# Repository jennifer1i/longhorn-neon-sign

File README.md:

# Neon Sign Interface Board RevB - Jennifer Li

## Board Description
- Compact 2-layer PCB for PWM-controlled LED driving using nMOSFET switching and onboard 12V->5V buck regulation. Revision of neon sign project from Summer 2025 with stronger consideration for manufacturability, testability, thermal management, compact routing, and aesthetics. 
## Features
- 12V input power architecture
- 12V->5V integrated buck converter
- Multi-channel nMOSFET LED control
- Arduino-Nano based LED toggling and dimming
- Optimized for compact and clean routing
- SMT/SMD and THT assembly
- Testpoints for GND, 12V, 5V, and PWM
- Indicator LEDs with blank silkscreen for post-production debugging

## Design Notes
- The PCB was designed to be rectangular, optimizing balanced LED power distribution and component placement. Testpoints and button switches were placed along the sides for easier access in the debugging process. 
- For this design, I chose to have two LED output terminals after evaluating the maximum load requirement of the targeted LED strips. The strips I chose draw up to 5A, and thus my output circuits were designed to handle up to roughly 2.5A.
- In addition, these two terminals were placed on opposite ends of the PCB's length to simplify high-current routing, reduce congestion, and distribute power evenly across the final neon sign product without unecessary harnessing cross-over. To accomodate this placement, I used a 12V pour on the top layer in an area with minimal top-layer GND pads and minimal top-layer routing. Thus, I could provide a clean low-impedance power distribution between the input stage and the LED ouptut terminal on the opposite end of the board. 
  
## PCB Specificaitions
- Layers: 2
- PCB Thickness: 1.6 mm
- Assembly: SMT/SMD and THT
- Designed in KiCad

## Future Improvements
- Switch to addressable LED strips for firmware-controlled animation and color effects
- Transition to a fully integrated MCU system (ESP32) directly mounted on the PCB
- Use lower-profile connectors like Molex Nanofits instead of screw terminals
- Rework the user input interface, using more ergonomic control interfaces like potentiometers, rotary encoders, or low-profile switches
- Add additional protection circuitry including input fuses, TVS diodes, reverse-polarity protection, and overvoltage and undervoltage protection
- Implement per-channel current sensing and thermal monitoring
- Enable PG pin for buck converter and add output sensing

## Top Layer

## Back Layer

## 3D Render

## Root Schematic

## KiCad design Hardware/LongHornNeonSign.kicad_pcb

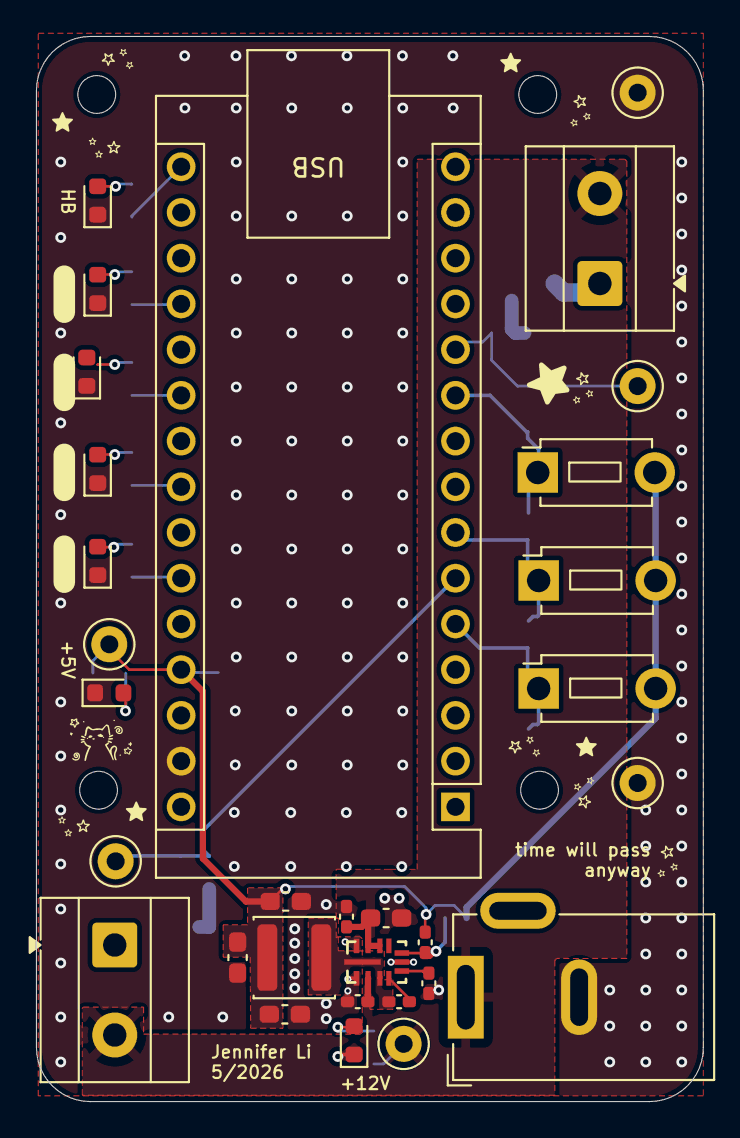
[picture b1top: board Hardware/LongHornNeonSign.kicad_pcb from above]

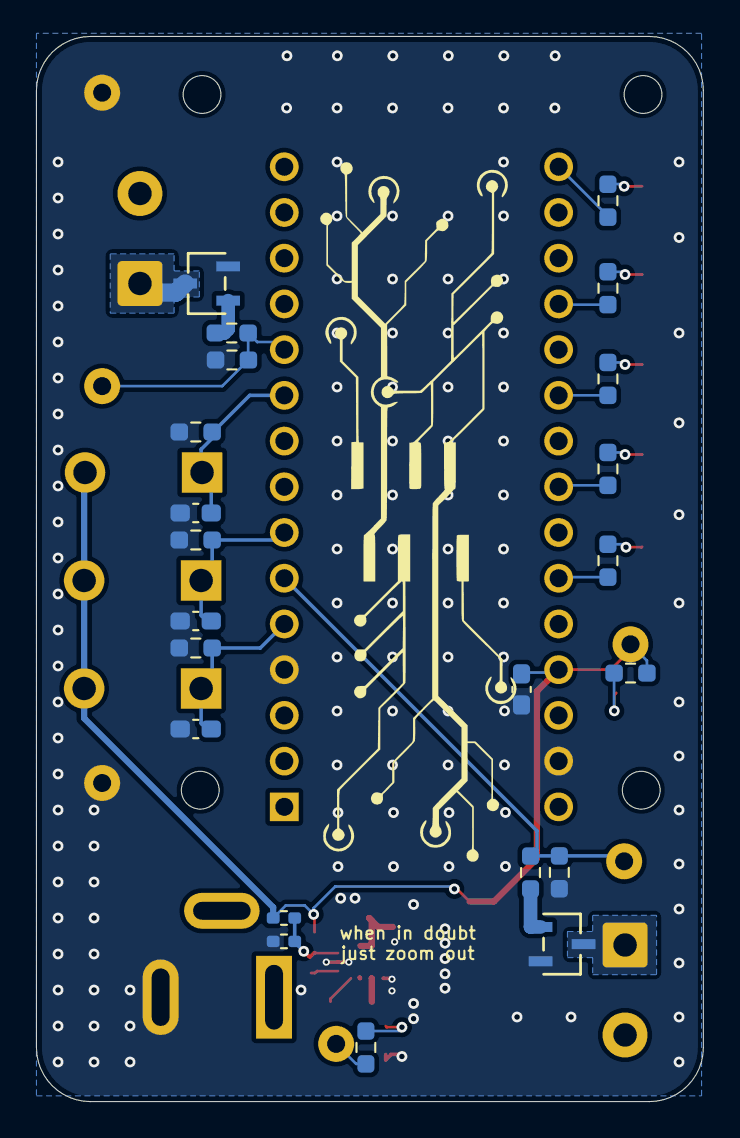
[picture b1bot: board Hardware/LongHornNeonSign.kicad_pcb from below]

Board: 2 copper layers, 37.0 x 59.2 mm, 57 parts (22 on the bottom side), 28 nets.

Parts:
A1: Arduino Nano; Arduino_Nano
C1, C11, C12, C13: 0.1uF; C_0603_1608Metric_Pad1.08x0.95mm_HandSolder
C2: 4.7u; C_0603_1608Metric_Pad1.08x0.95mm_HandSolder
C3, C4: 220n; C_0402_1005Metric_Pad0.74x0.62mm_HandSolder
C5: 1u; C_0402_1005Metric_Pad0.74x0.62mm_HandSolder
C6: .1u; C_0402_1005Metric_Pad0.74x0.62mm_HandSolder
C7: 20p; C_0402_1005Metric_Pad0.74x0.62mm_HandSolder
C8, C9, C10: 22u; C_0603_1608Metric_Pad1.08x0.95mm_HandSolder
D1, D2: LED_0603_1608Metric
D3, D4: LED2; LED_0603_1608Metric
D5: LED1; LED_0603_1608Metric
D6: LED0; LED_0603_1608Metric
D7: Heartbeat; LED_0603_1608Metric
H1, H2, H3, H4: MountingHole; MountingHole_2.1mm
J1: Barrel_Jack_Switch; BarrelJack_GCT_DCJ200-10-A_Horizontal
J2, J5: Screw_Terminal_01x02; TerminalBlock_MetzConnect_Type055_RT01502HDWU_1x02_P5.00mm_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
L1: 15u; L_APV_ANR4030
Q1, Q4: AO3400A; SOT-23-3L_AOS
R1: 1kΩ; R_0603_1608Metric_Pad0.98x0.95mm_HandSolder
R2: 470Ω; R_0603_1608Metric_Pad0.98x0.95mm_HandSolder
R3: 100k; R_0402_1005Metric_Pad0.72x0.64mm_HandSolder
R4: 24.9k; R_0402_1005Metric_Pad0.72x0.64mm_HandSolder
R5, R10, R13, R14, R15: 10kΩ; R_0603_1608Metric_Pad0.98x0.95mm_HandSolder
R7, R12: 220; R_0603_1608Metric_Pad0.98x0.95mm_HandSolder
R16, R17, R18, R19, R20: 120; R_0603_1608Metric_Pad0.98x0.95mm_HandSolder
S1, S2, S3: SW_Push; SW_PUSH_1P1T_6x3.5mm_H4.3_APEM_MJTP1243
TP1, TP2: GND; TestPoint_Keystone_5000-5004_Miniature
TP3: +12V; TestPoint_Keystone_5000-5004_Miniature
TP4: +5V; TestPoint_Keystone_5000-5004_Miniature
TP5: PWM1; TestPoint_Keystone_5000-5004_Miniature
TP8: PWM4; TestPoint_Keystone_5000-5004_Miniature
U1: LMR34215FSC5RNXRQ1; RNX12_TEX

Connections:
+5V: A1.27 (+5V), C1.1, C7.2, C8.2, C9.2, C10.2, L1.2, R2.1, R3.1, S1.2, S2.2, S3.2, TP4.1
+12V: C2.2, C3.2, C4.2, J1.1, J2.2, J5.2, R1.1, TP3.1, U1.2 (VIN), U1.9 (EN), U1.10 (VIN)
/12V-5V Buck Converter/SW: C6.2, L1.1, U1.3 (NC), U1.12 (SW)
/Debug LEDs/LED1: A1.19 (A0), R19.1
/Debug LEDs/LED2: A1.21 (A2), R18.1
/Debug LEDs/LED3: A1.23 (A4), R17.1
/Debug LEDs/LED4: A1.25 (A6), R16.1
/HIGHER: A1.7 (D4), C12.2, R14.1, S2.1
/LED_HB: A1.16 (D13), R20.1
/LOWER: A1.10 (D7), C13.2, R15.1, S3.1
/PWM1: A1.6 (D3), R5.1, R7.1, TP5.1
/PWM4: A1.11 (D8), R10.1, R12.1, TP8.1
/TOGGLE: A1.5 (D2), C11.2, R13.1, S1.1
GND: A1.4 (GND), A1.29 (GND), C1.2, C2.1, C3.1, C4.1, C5.1, C8.1, C9.1, C10.1, C11.1, C12.1, C13.1, D1.1 (K), D2.1 (K), D3.1 (K), D4.1 (K), D5.1 (K), D6.1 (K), D7.1 (K), J1.2, Q1.2 (S), Q4.2 (S), R4.2, R5.2, R10.2, R13.2, R14.2, R15.2, TP1.1, TP2.1, U1.1 (PGND), U1.6 (AGND), U1.11 (PGND)
unnamed: D1.2 (A), R1.2
unnamed: D2.2 (A), R2.2
unnamed: D3.2 (A), R16.2
unnamed: D4.2 (A), R17.2
unnamed: D5.2 (A), R18.2
unnamed: D6.2 (A), R19.2
unnamed: D7.2 (A), R20.2
unnamed: J2.1, Q1.3 (D)
unnamed: J5.1, Q4.3 (D)
unnamed: Q1.1 (G), R7.2
unnamed: Q4.1 (G), R12.2
unnamed: C6.1, U1.4 (BOOT)
unnamed: C7.1, R3.2, R4.1, U1.7 (FB)
unnamed: C5.2, U1.5 (VCC)

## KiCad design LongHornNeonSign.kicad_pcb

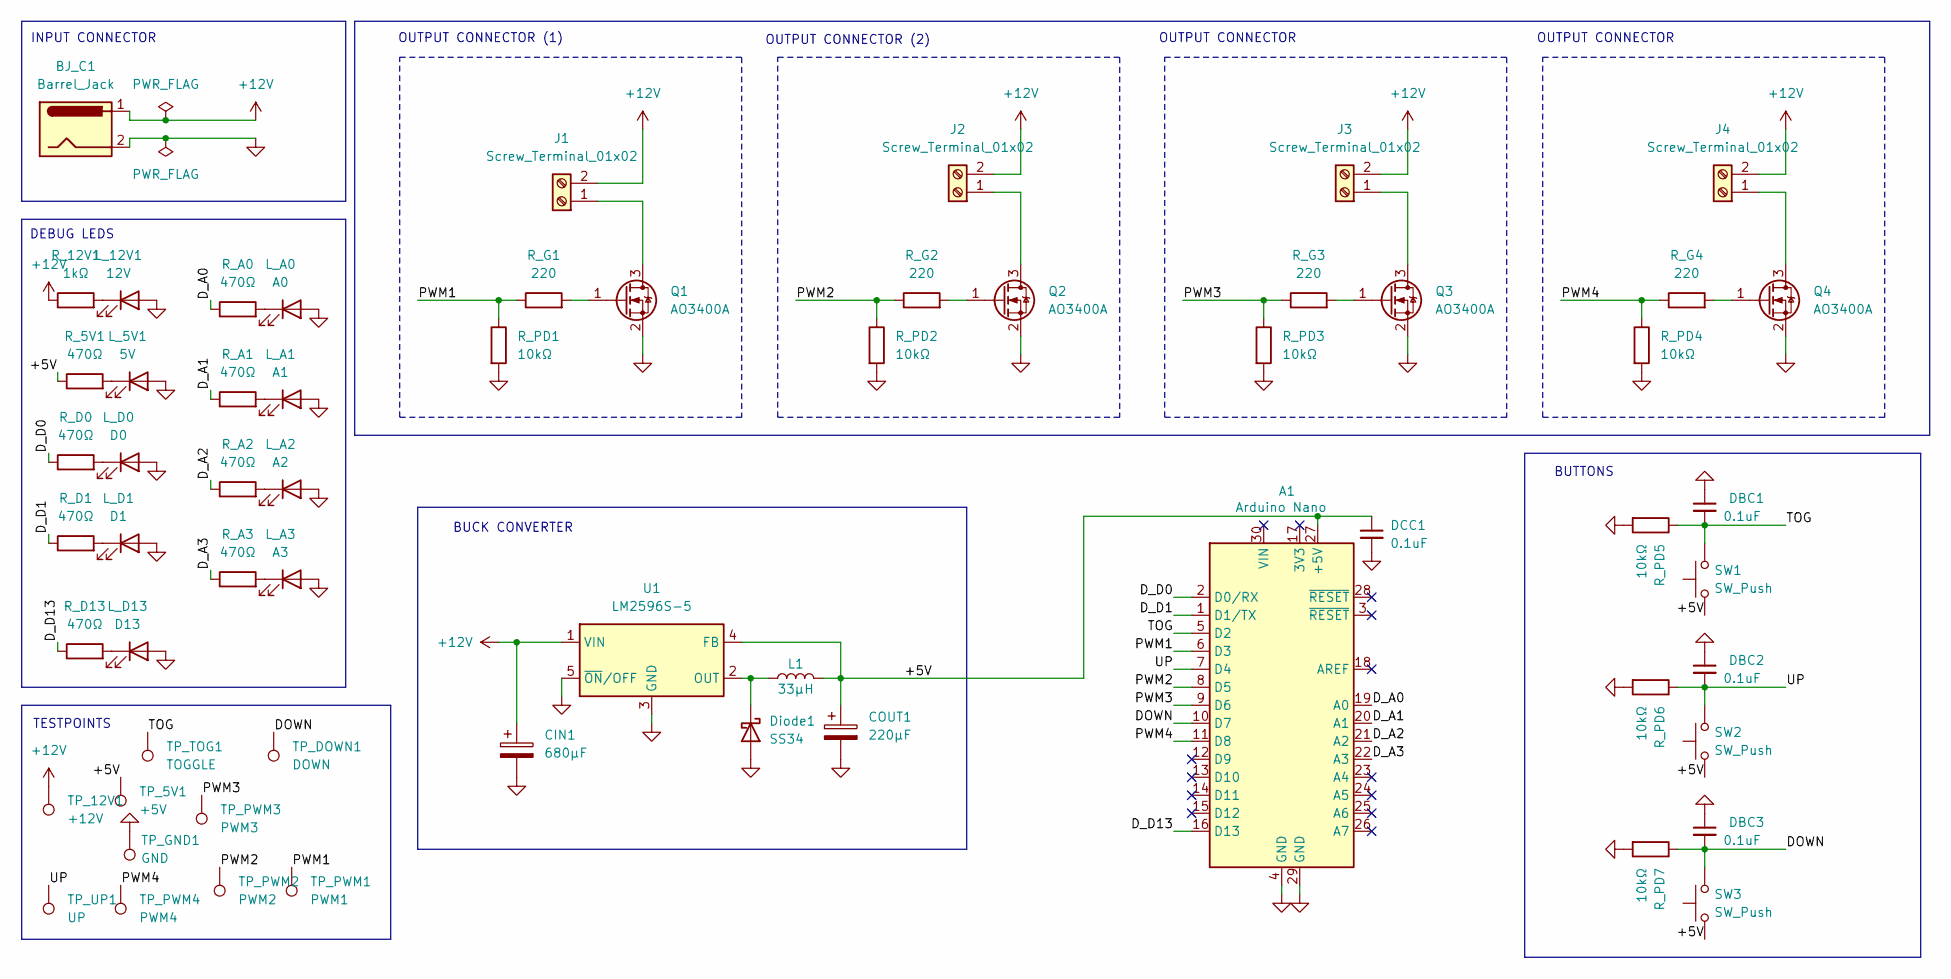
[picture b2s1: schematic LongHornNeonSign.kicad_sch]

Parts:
A1: Arduino Nano; Arduino_Nano
BJ_C1: Barrel_Jack; BarrelJack_CUI_PJ-102AH_Horizontal; LCSC C381116
CIN1: 680μF; CP_Elec_10x10; LCSC C2902805
COUT1: 220μF; CP_Elec_6.3x7.7; LCSC C2827940
DBC1, DBC2, DBC3: 0.1uF; C_0603_1608Metric; LCSC C14663
DCC1: 0.1uF; C_0603_1608Metric; LCSC C14663
Diode1: SS34; D_SMA; LCSC C8678
J1, J2, J3, J4: Screw_Terminal_01x02; TerminalBlock_Phoenix_MKDS-1,5-2-5.08_1x02_P5.08mm_Horizont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; LCSC C8465
L1: 33μH; L_12x12mm_H8mm; LCSC C2929502
L_5V1: 5V; LED_0805_2012Metric; LCSC C375456
L_12V1: 12V; LED_0805_2012Metric; LCSC C375456
L_A0: A0; LED_0805_2012Metric; LCSC C375456
L_A1: A1; LED_0805_2012Metric; LCSC C375456
L_A2: A2; LED_0805_2012Metric; LCSC C375456
L_A3: A3; LED_0805_2012Metric; LCSC C375456
L_D0: D0; LED_0805_2012Metric; LCSC C375456
L_D1: D1; LED_0805_2012Metric; LCSC C375456
L_D13: D13; LED_0805_2012Metric; LCSC C375456
Q1, Q2, Q3, Q4: AO3400A; SOT-23; LCSC C20917
R_5V1: 470Ω; R_0805_2012Metric; LCSC C114564
R_12V1: 1kΩ; R_0805_2012Metric; LCSC C95781
R_A0, R_A1, R_A2, R_A3: 470Ω; R_0805_2012Metric; LCSC C114564
R_D0, R_D1, R_D13: 470Ω; R_0805_2012Metric; LCSC C114564
R_G1, R_G2, R_G3, R_G4: 220; R_0805_2012Metric; LCSC C104105
R_PD1, R_PD2, R_PD3, R_PD4, R_PD5, R_PD6, R_PD7: 10kΩ; R_0805_2012Metric; LCSC C17414
SW1, SW2, SW3: SW_Push; SW_Tactile_SPST_NO_Straight_CK_PTS636Sx25SMTRLFS; LCSC C10852
TP_5V1: +5V; PinHeader_1x01_P2.54mm_Vertical
TP_12V1: +12V; PinHeader_1x01_P2.54mm_Vertical
TP_DOWN1: DOWN; PinHeader_1x01_P2.54mm_Vertical
TP_GND1: GND; PinHeader_1x01_P2.54mm_Vertical
TP_PWM1: PWM1; PinHeader_1x01_P2.54mm_Vertical
TP_PWM2: PWM2; PinHeader_1x01_P2.54mm_Vertical
TP_PWM3: PWM3; PinHeader_1x01_P2.54mm_Vertical
TP_PWM4: PWM4; PinHeader_1x01_P2.54mm_Vertical
TP_TOG1: TOGGLE; PinHeader_1x01_P2.54mm_Vertical
TP_UP1: UP; PinHeader_1x01_P2.54mm_Vertical
U1: LM2596S-5; TO-263-5_TabPin3; LCSC C116713

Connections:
+12V: BJ_C1.1, CIN1.1, J1.2, J2.2, J3.2, J4.2, R_12V1.1, TP_12V1.1, U1.1 (VIN)
/+5V: A1.27 (+5V), COUT1.1, DCC1.1, L1.2, R_5V1.1, SW1.1, SW2.1, SW3.1, TP_5V1.1, U1.4 (FB)
/DOWN: A1.10 (D7), DBC3.2, R_PD7.1, SW3.2, TP_DOWN1.1
/D_A0: A1.19 (A0), R_A0.1
/D_A1: A1.20 (A1), R_A1.1
/D_A2: A1.21 (A2), R_A2.1
/D_A3: A1.22 (A3), R_A3.1
/D_D0: A1.2 (D0/RX), R_D0.1
/D_D1: A1.1 (D1/TX), R_D1.1
/D_D13: A1.16 (D13), R_D13.1
/PWM1: A1.6 (D3), R_G1.1, R_PD1.1, TP_PWM1.1
/PWM2: A1.8 (D5), R_G2.1, R_PD2.1, TP_PWM2.1
/PWM3: A1.9 (D6), R_G3.1, R_PD3.1, TP_PWM3.1
/PWM4: A1.11 (D8), R_G4.1, R_PD4.1, TP_PWM4.1
/TOG: A1.5 (D2), DBC1.2, R_PD5.1, SW1.2, TP_TOG1.1
/UP: A1.7 (D4), DBC2.2, R_PD6.1, SW2.2, TP_UP1.1
GND: A1.4 (GND), A1.29 (GND), BJ_C1.2, CIN1.2, COUT1.2, DBC1.1, DBC2.1, DBC3.1, DCC1.2, Diode1.2 (A), L_5V1.2 (A), L_12V1.2 (A), L_A0.2 (A), L_A1.2 (A), L_A2.2 (A), L_A3.2 (A), L_D0.2 (A), L_D1.2 (A), L_D13.2 (A), Q1.2 (S), Q2.2 (S), Q3.2 (S), Q4.2 (S), R_PD1.2, R_PD2.2, R_PD3.2, R_PD4.2, R_PD5.2, R_PD6.2, R_PD7.2, TP_GND1.1, U1.3 (GND), U1.5 (~ON/OFF)
unnamed: Diode1.1 (K), L1.1, U1.2 (OUT)
unnamed: J1.1, Q1.3 (D)
unnamed: J2.1, Q2.3 (D)
unnamed: J3.1, Q3.3 (D)
unnamed: J4.1, Q4.3 (D)
unnamed: L_5V1.1 (K), R_5V1.2
unnamed: L_12V1.1 (K), R_12V1.2
unnamed: L_A0.1 (K), R_A0.2
unnamed: L_A1.1 (K), R_A1.2
unnamed: L_A2.1 (K), R_A2.2
unnamed: L_A3.1 (K), R_A3.2
unnamed: L_D0.1 (K), R_D0.2
unnamed: L_D1.1 (K), R_D1.2
unnamed: L_D13.1 (K), R_D13.2
unnamed: Q1.1 (G), R_G1.2
unnamed: Q2.1 (G), R_G2.2
unnamed: Q3.1 (G), R_G3.2
unnamed: Q4.1 (G), R_G4.2

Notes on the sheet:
BUCK CONVERTER
TESTPOINTS
BUTTONS
OUTPUT CONNECTOR
INPUT CONNECTOR
OUTPUT CONNECTOR (1)
OUTPUT CONNECTOR (2)
DEBUG LEDS

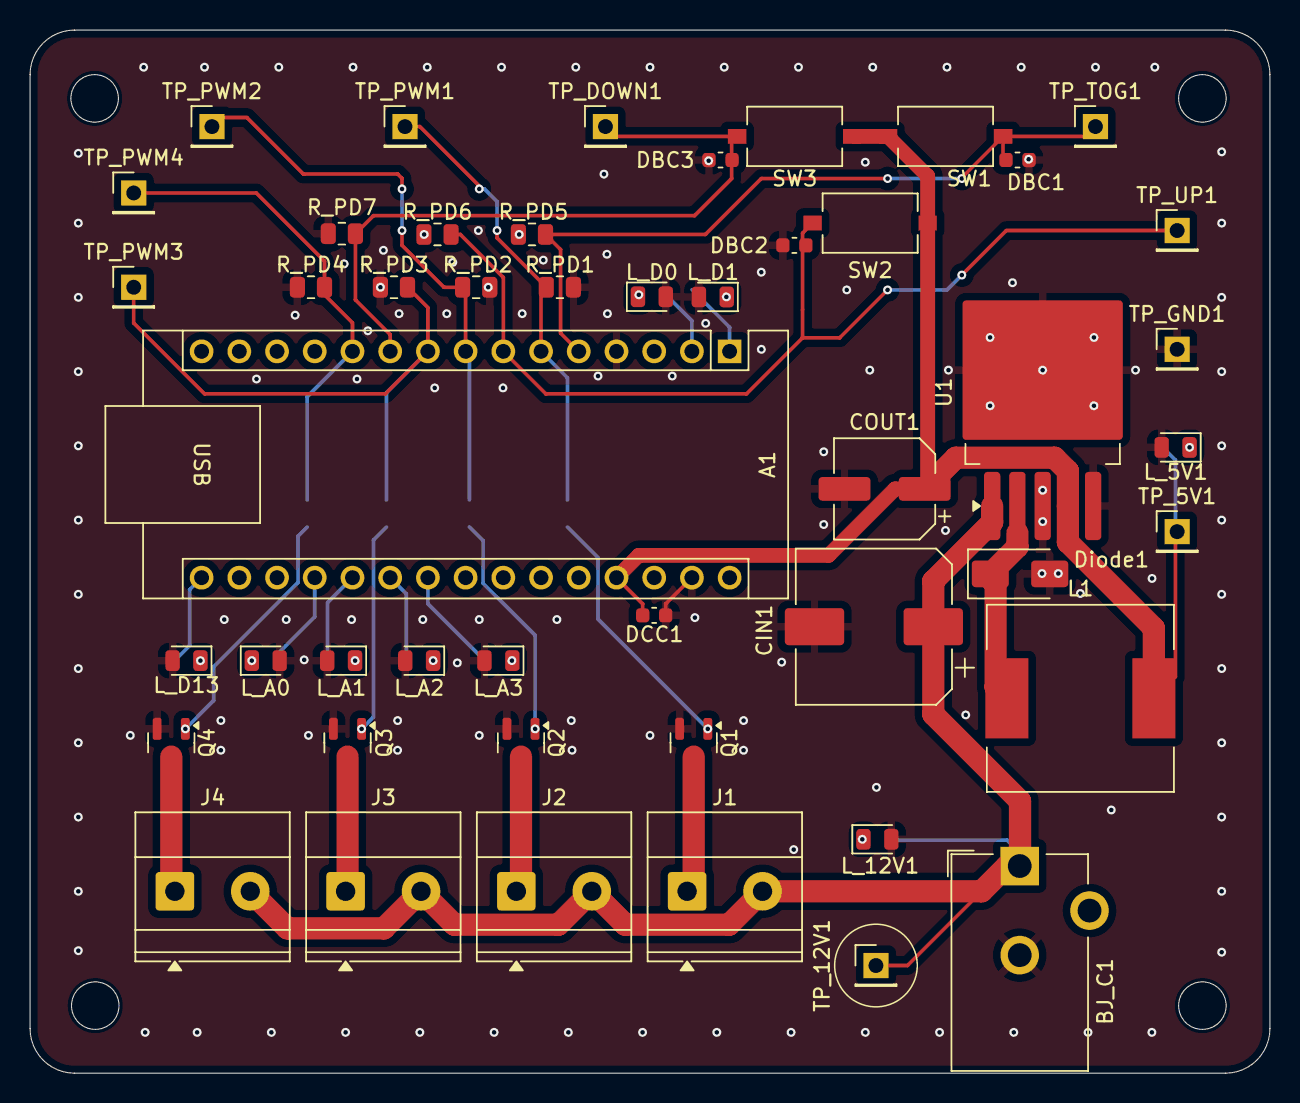
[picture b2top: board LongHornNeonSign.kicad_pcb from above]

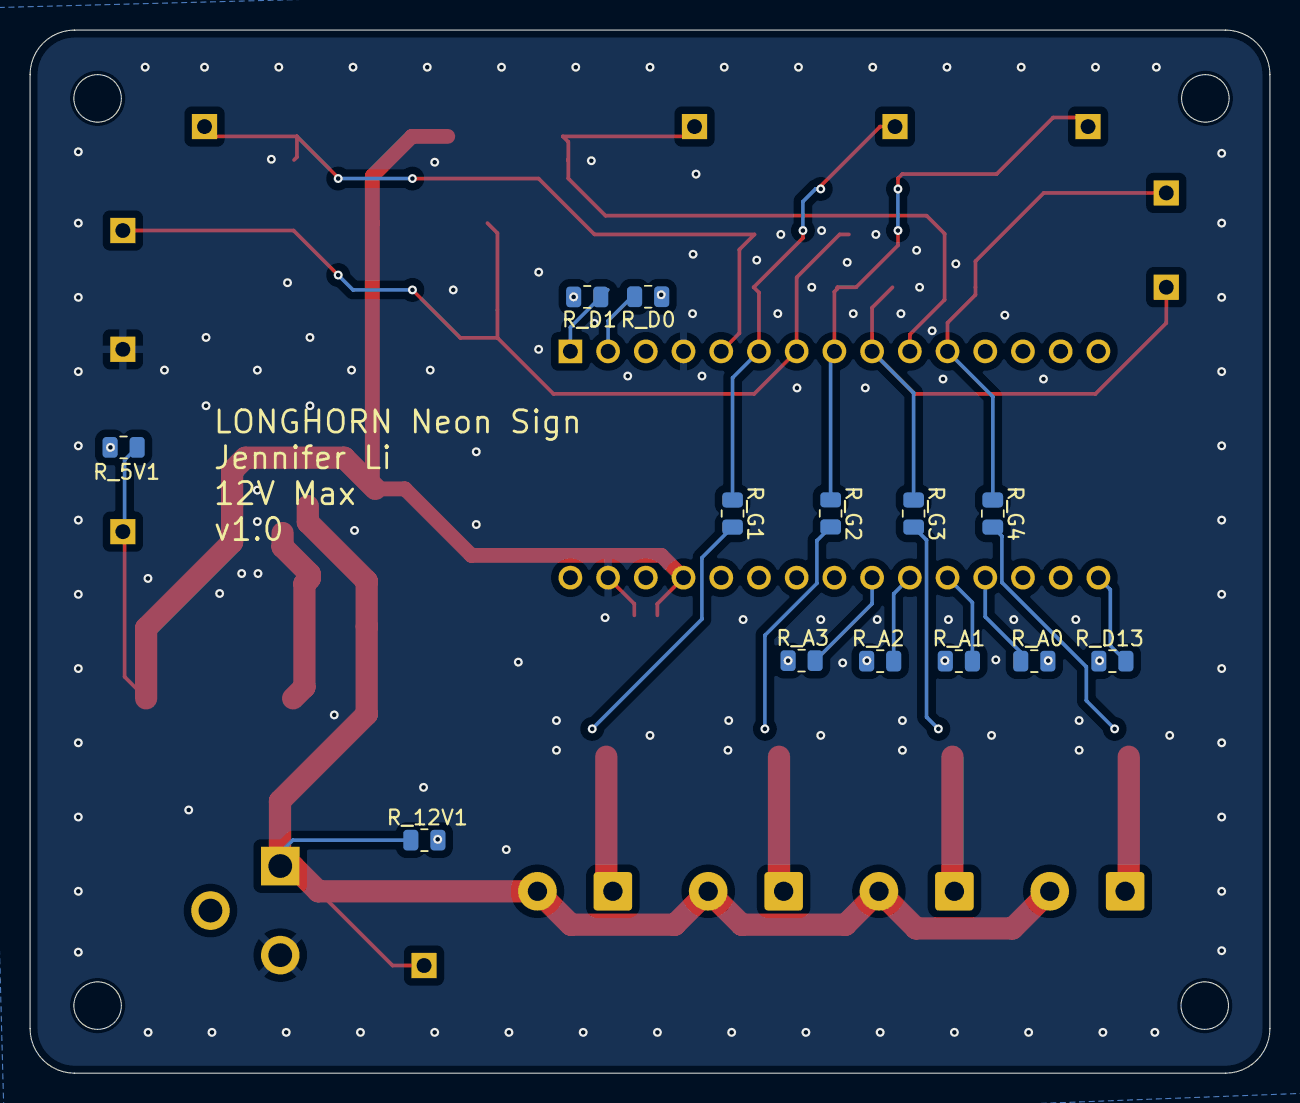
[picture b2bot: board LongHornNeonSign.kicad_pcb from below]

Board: 2 copper layers, 83.5 x 70.2 mm, 64 parts (13 on the bottom side), 35 nets.

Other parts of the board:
M1, M1#2, M1#3: MountingHole_3.2mm_M3

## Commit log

2025-07-08 Fixed schematic
2025-07-12 update sch
2025-07-12 Added testpoint example
2025-07-13 sch done
2025-07-21 updated pcb
2025-07-21 update pcb
2025-08-30 pictures
2026-05-12 May 12 2026 run it back
2026-05-19 done layout 5/18/2026
2026-05-19 clean up
2026-05-19 small delete
2026-05-19 finalize PCB, added images and silkscreen text and 3D models
2026-05-19 push RevB's README and edit schematic specs
2026-05-19 revB
2026-05-19 add images
